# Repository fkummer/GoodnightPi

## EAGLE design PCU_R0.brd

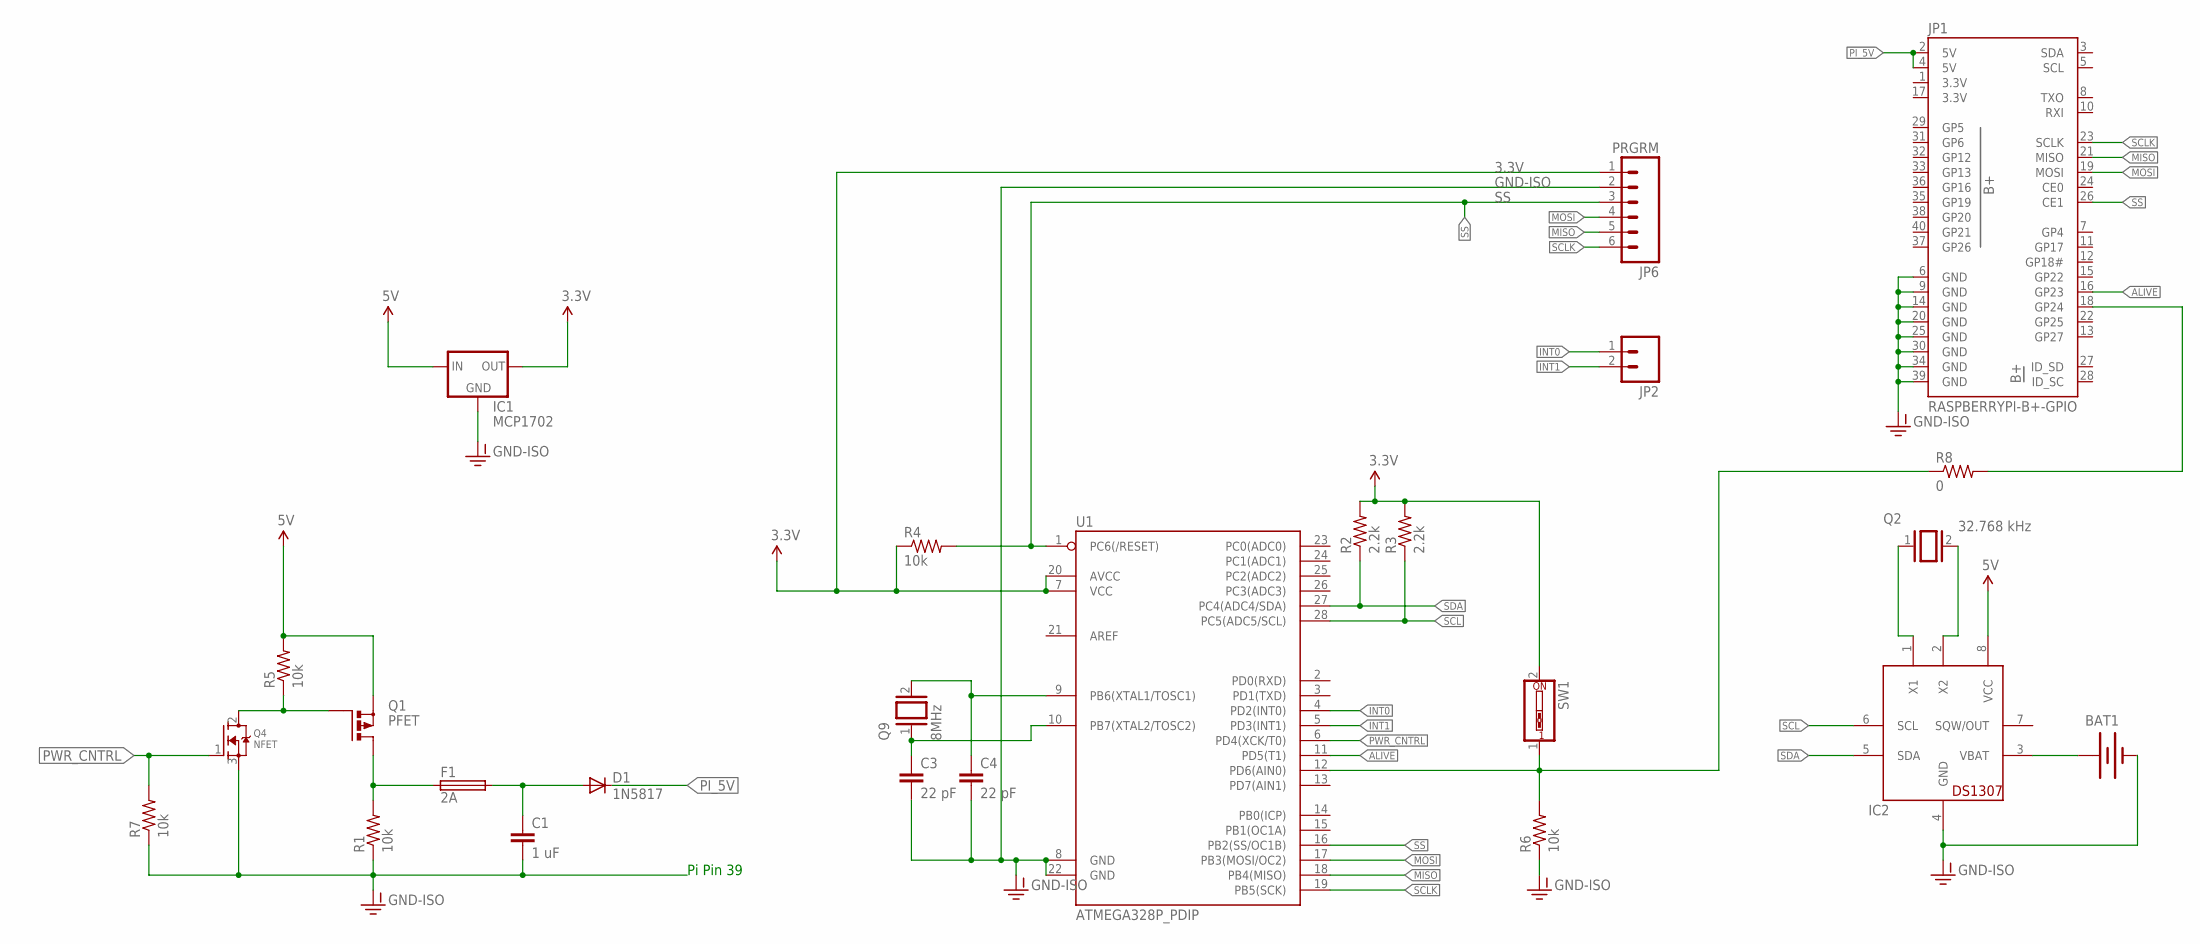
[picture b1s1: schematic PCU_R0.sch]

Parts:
BAT1: BATTERY12MM; BATTCON_12MM
C1: 1 uF; C2.5-3
C3, C4: 22 pF; C2.5-3
D1: 1N5817; DO41-10
F1: 2A; PICOFUSE
IC1: MCP1702; TO92
IC2: DS1307; DIL08
JP1: RASPBERRYPI-B+-GPIO; 2X20-SHROUDED
JP2: M02PTH; 1X02
JP6: PRGRM; 1X06
Q1: PFET; TO220BV
Q2: 32.768 kHz; QS
Q4: NFET; TO220V
Q9: 8MHz; QS
R1, R4, R5, R6, R7: 10k; 1206
R2, R3: 2.2k; 1206
R8: 0; 1206
SW1: SW_DIP-1; EDG-01
U1: ATMEGA328P_PDIP; DIL28-3

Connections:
3.3V: IC1.3 (OUT), JP1.1 (3.3V), JP1.17 (3.3V), JP6.1, R2.2, R3.2, R4.1, SW1.2, U1.7 (VCC), U1.20 (AVCC)
5V: IC1.2 (IN), IC2.8 (VCC), Q1.S, R5.2
ALIVE: JP1.16 (GP23), U1.11 (PD5(T1))
GND-ISO: BAT1.GND (-), C1.2, C3.2, C4.2, IC1.1 (GND), IC2.4 (GND), JP1.6 (GND), JP1.9 (GND), JP1.14 (GND), JP1.20 (GND), JP1.25 (GND), JP1.30 (GND), JP1.34 (GND), JP1.39 (GND), JP6.2, Q4.3 (S), R1.1, R6.1, R7.1, U1.8 (GND), U1.22 (GND)
INT0: JP2.1, U1.4 (PD2(INT0))
INT1: JP2.2, U1.5 (PD3(INT1))
MISO: JP1.21 (MISO), JP6.5, U1.18 (PB4(MISO))
MOSI: JP1.19 (MOSI), JP6.4, U1.17 (PB3(MOSI/OC2))
unnamed: F1.1, Q1.D, R1.2
unnamed: C1.1, D1.A, F1.2
unnamed: IC2.1 (X1), Q2.1
unnamed: IC2.2 (X2), Q2.2
unnamed: BAT1.PWR@1 (+), IC2.3 (VBAT)
unnamed: Q1.G, Q4.2 (D), R5.1
unnamed: JP1.18 (GP24), R8.2
unnamed: R6.2, R8.1, SW1.1, U1.12 (PD6(AIN0))
unnamed: C3.1, Q9.1, U1.10 (PB7(XTAL2/TOSC2))
unnamed: C4.1, Q9.2, U1.9 (PB6(XTAL1/TOSC1))
PI_5V: D1.C, JP1.2 (5V), JP1.4 (5V)
PWR_CNTRL: Q4.1 (G), R7.2, U1.6 (PD4(XCK/T0))
SCL: IC2.6 (SCL), R3.1, U1.28 (PC5(ADC5/SCL))
SCLK: JP1.23 (SCLK), JP6.6, U1.19 (PB5(SCK))
SDA: IC2.5 (SDA), R2.1, U1.27 (PC4(ADC4/SDA))
SS: JP1.26 (CE1), JP6.3, R4.2, U1.1 (PC6(/RESET)), U1.16 (PB2(SS/OC1B))

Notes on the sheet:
Pi Pin 39

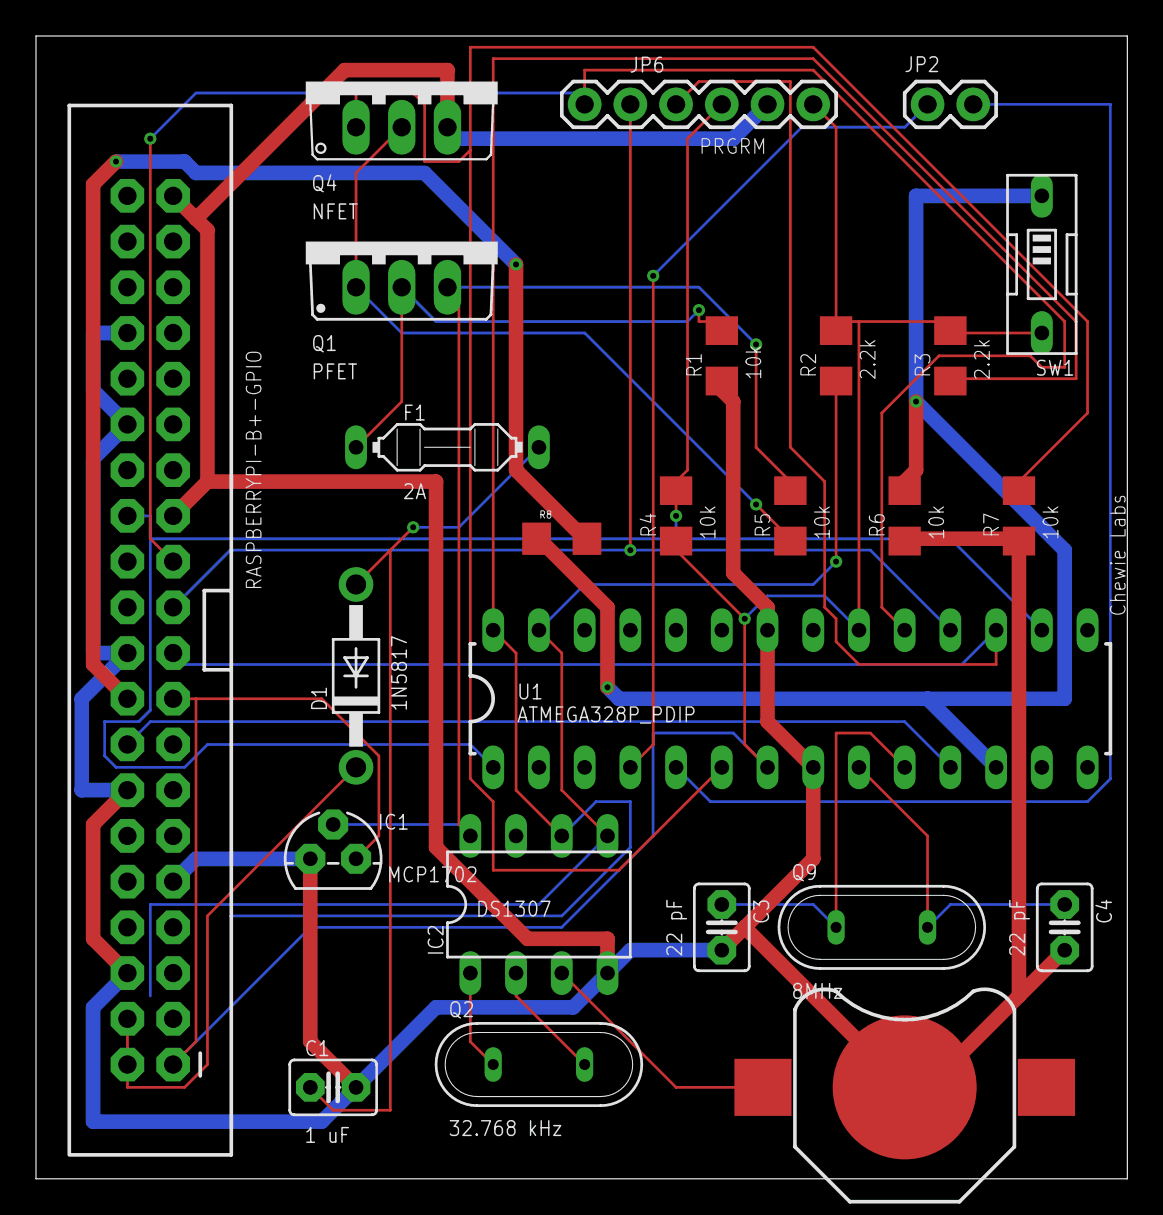
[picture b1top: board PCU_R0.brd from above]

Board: 2 copper layers, 60.6 x 63.5 mm, 25 parts (0 on the bottom side), 24 nets.

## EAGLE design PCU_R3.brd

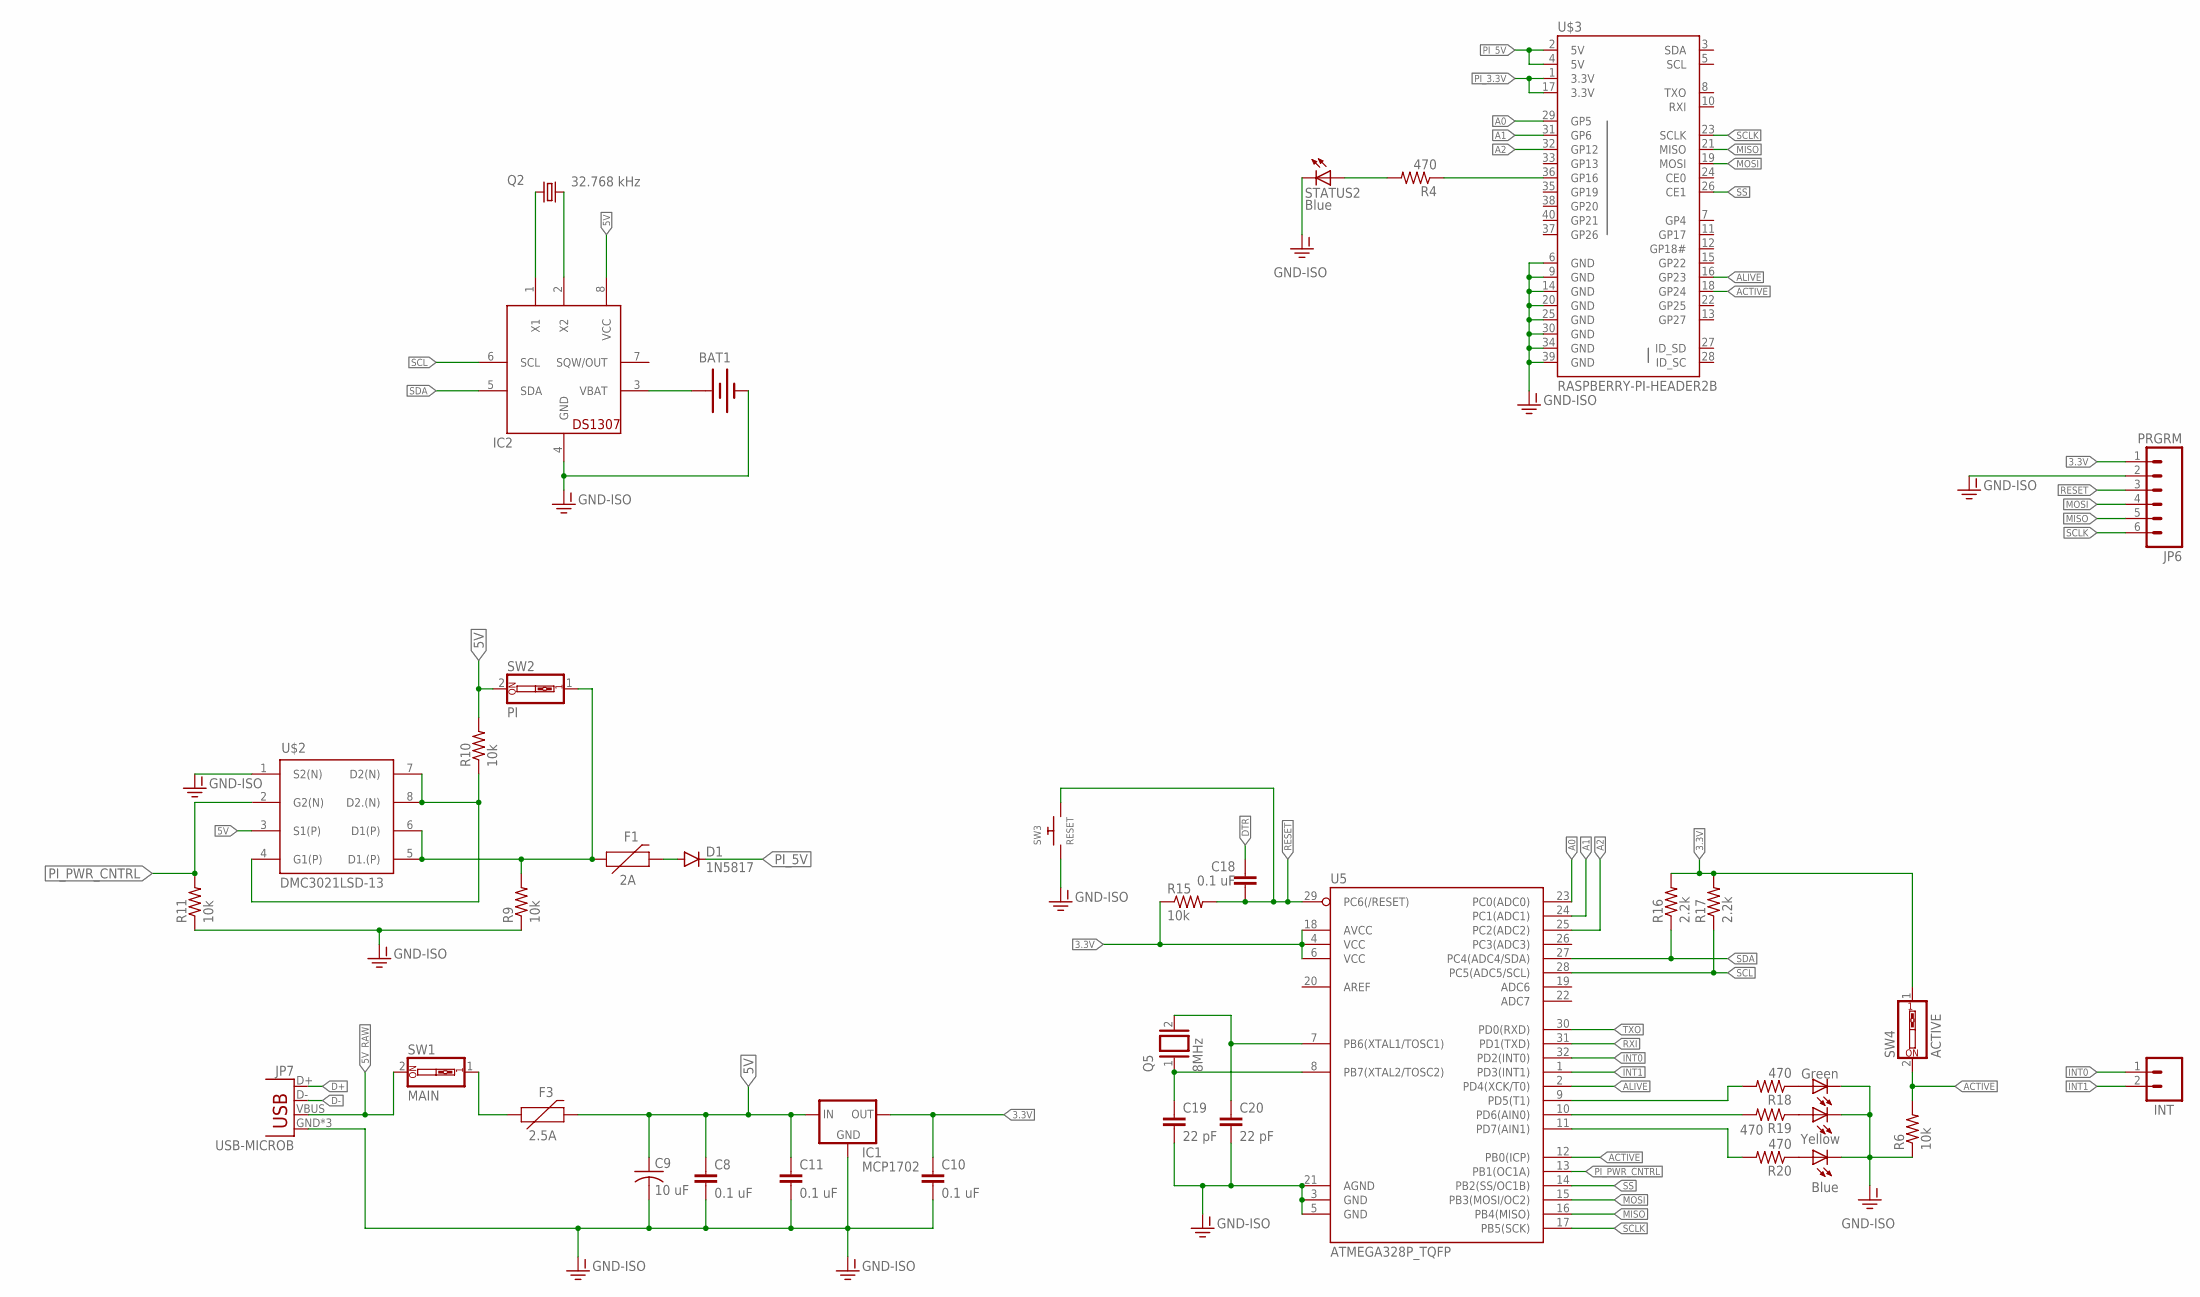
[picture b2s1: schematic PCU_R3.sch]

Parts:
BAT1: BATTERY12MM; BATTCON_12MM
C8, C10, C11, C18: 0.1 uF; 1206
C9: 10 uF; C1206
C19, C20: 22 pF; 1206
D1: 1N5817; DIODE-1N4001
F1: 2A; 1206
F3: 2.5A; 1206
IC1: MCP1702; TO92
IC2: DS1307; DIL08
INT: M02PTH; 1X02
JP6: PRGRM; 1X06
JP7: USB-MICROB
LED6: Green; CHIPLED_1206
LED7: Yellow; CHIPLED_1206
LED8: Blue; CHIPLED_1206
Q2: 32.768 kHz; TC38H
Q5: 8MHz; QS
R4, R18, R19, R20: 470; 1206
R6, R15: 10k; 1206
R9, R10, R11: 10k; R1206
R16, R17: 2.2k; 1206
STATUS2: Blue; CHIPLED_1206
SW1: MAIN; EDG-01
SW2: PI; EDG-01
SW3: RESET; PUSHBUTTON_SMD_SJ
SW4: ACTIVE; EDG-01
U5: ATMEGA328P_TQFP; TQFP32-08
U$2: DMC3021LSD-13; SOIC-8
U$3: RASPBERRY-PI-HEADER2B; 2X20-NOSILK

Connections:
3.3V: C10.1, IC1.3 (OUT), JP6.1, R15.1, R16.2, R17.2, SW4.1, U5.4 (VCC), U5.6 (VCC), U5.18 (AVCC)
5V: C8.1, C9.1, C11.1, F3.2, IC1.2 (IN), IC2.8 (VCC), R10.2, SW2.2, U$2.3 (S1(P))
5V_RAW: JP7.VBUS, SW1.2
5V_SWITCH: F3.1, SW1.1
A0: U5.23 (PC0(ADC0)), U$3.29 (GP5)
A1: U5.24 (PC1(ADC1)), U$3.31 (GP6)
A2: U5.25 (PC2(ADC2)), U$3.32 (GP12)
ACTIVE: R6.2, SW4.2, U5.12 (PB0(ICP)), U$3.18 (GP24)
ALIVE: U5.2 (PD4(XCK/T0)), U$3.16 (GP23)
D+: JP7.D+
D-: JP7.D-
DTR: C18.1
FUSE_DIODE_PI: D1.A, F1.2
GND-ISO: BAT1.GND (-), C8.2, C9.2, C10.2, C11.2, C19.2, C20.2, IC1.1 (GND), IC2.4 (GND), JP6.2, JP7.GND, JP7.MT1 (GND), JP7.MT2 (GND), LED6.C, LED7.C, LED8.C, R6.1, R9.1, R11.1, STATUS2.C, SW3.P$1, U5.3 (GND), U5.5 (GND), U5.21 (AGND), U$2.1 (S2(N)), U$3.6 (GND), U$3.9 (GND), U$3.14 (GND), U$3.20 (GND), U$3.25 (GND), U$3.30 (GND), U$3.34 (GND), U$3.39 (GND)
GP16: R4.1, U$3.36 (GP16)
INT0: INT.1, U5.32 (PD2(INT0))
INT1: INT.2, U5.1 (PD3(INT1))
MISO: JP6.5, U5.16 (PB4(MISO)), U$3.21 (MISO)
MOSI: JP6.4, U5.15 (PB3(MOSI/OC2)), U$3.19 (MOSI)
unnamed: IC2.1 (X1), Q2.1
unnamed: IC2.2 (X2), Q2.2
unnamed: BAT1.PWR@1 (+), IC2.3 (VBAT)
unnamed: R4.2, STATUS2.A
unnamed: LED6.A, R18.1
unnamed: LED7.A, R19.1
unnamed: LED8.A, R20.1
PD5: R18.2, U5.9 (PD5(T1))
PD6: R19.2, U5.10 (PD6(AIN0))
PD7: R20.2, U5.11 (PD7(AIN1))
PI_3.3V: U$3.1 (3.3V), U$3.17 (3.3V)
PI_5V: D1.C, U$3.2 (5V), U$3.4 (5V)
PI_N_DRAIN: R10.1, U$2.4 (G1(P)), U$2.7 (D2(N)), U$2.8 (D2.(N))
PI_PWR_CNTRL: R11.2, U5.13 (PB1(OC1A)), U$2.2 (G2(N))
PI_P_DRAIN: F1.1, R9.2, SW2.1, U$2.5 (D1.(P)), U$2.6 (D1(P))
RESET: C18.2, JP6.3, R15.2, SW3.P$2, U5.29 (PC6(/RESET))
RXI: U5.31 (PD1(TXD))
SCL: IC2.6 (SCL), R17.1, U5.28 (PC5(ADC5/SCL))
SCLK: JP6.6, U5.17 (PB5(SCK)), U$3.23 (SCLK)
SDA: IC2.5 (SDA), R16.1, U5.27 (PC4(ADC4/SDA))
SS: U5.14 (PB2(SS/OC1B)), U$3.26 (CE1)
TXO: U5.30 (PD0(RXD))
XTAL1: C20.1, Q5.2, U5.7 (PB6(XTAL1/TOSC1))
XTAL2: C19.1, Q5.1, U5.8 (PB7(XTAL2/TOSC2))

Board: 2 copper layers, 40 parts (0 on the bottom side), 38 nets, no tracks yet.

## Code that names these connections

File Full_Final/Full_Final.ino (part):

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volatile byte supress_int = 0;

//Is Pi alive
boolean alive = 1;

//Do we want to turn off the power when we get the chance?
boolean gotoSleep = 0;
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long timeInterval = 0;

//Is int0 enabled
byte int0 = 0;

//Is int1 enable
byte int1 = 0;

//timer wants us to get up
byte timer_woke = 0;
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
#define LED   7
#define PACKET_LEN 11
#define ALIVE 4
#define PWR_CNTRL 9
#define INT0 2
#define INT1 3
#define GREEN 6
#define YELLOW 5

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      if(buff[5] == 1){
        Serial.println("\n\ntoggle int0");
        Serial.print("INT0:");
        int0 ^= 1;
        Serial.println(int0);
        Serial.println("\n\n");
        
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      //int1 enable/disable
      if(buff[7] == 1){
        Serial.println("toggle int1");
        int1 ^= 1;
      }
      
      break;
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  pinMode(LED, OUTPUT);
  pinMode(GREEN, OUTPUT);
  pinMode(YELLOW, OUTPUT);
  pinMode(PWR_CNTRL, OUTPUT);
  pinMode(ALIVE, INPUT);
  pinMode(INT0, INPUT);
  pinMode(INT1, INPUT);
  
  

  
  attachInterrupt(digitalPinToInterrupt(INT0), int0_handler, RISING);
  attachInterrupt(digitalPinToInterrupt(INT1), int1_handler, RISING);
 
  digitalWrite(GREEN, LOW);
  digitalWrite(YELLOW, HIGH);
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    if(!alive){
      Serial.println("Beep");
      delay(5000); //Wait to make sure Pi is shutdown
      //attachInterrupt(digitalPinToInterrupt(INT0), int0_handler, RISING);
      //attachInterrupt(digitalPinToInterrupt(INT1), int1_handler, RISING);
      turnOffPower();
      wait_for_wake = 1;
      if(timeInterval != 0){
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     Serial.println("BRING!");
     ledState = ledState ^ 1;
     wait_for_wake = 0;
     //detachInterrupt(digitalPinToInterrupt(INT0));
     //detachInterrupt(digitalPinToInterrupt(INT1));
     digitalWrite(LED,ledState);
     turnOnPower();
  }else{
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
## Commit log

2016-11-15 Init Commit
2016-11-15 Changed startup to right path
2016-11-15 Added Arduino Code
2016-11-16 First SPI tests between Arduinos
2016-11-16 Added SPI with a slave response
2016-11-17 Initial communication between Pi and Arduino using SPI
2016-11-17 rtc blinking led
2016-11-17 Starting to make spi for 11 long packets
2016-11-17 Working on testing pi with longer packets
2016-11-18 Working on two way comms...
2016-11-18 Working on SPI
2016-11-21 spi tested from arduino side, 100ms delay required at Pi side to avoid dropping packets. Adding decision.c which parses the messages received
2016-11-29 Changing protocol
2016-11-29 More SPI
2016-11-30 Slave response working
2016-11-30 Began adding functionality to allow for SPI communication on Pi
2016-11-30 Added functions for sending all messages and receiving all responses on Pi
2016-11-30 Slave response on arduino end working, as well as circular buffer
2016-11-30 Handling setting opcodes and payloads now
2016-11-30 Made a change to help debug on fillEmpty
2016-11-30 Adding wake_check
2016-11-30 Tested wake check going to write call
2016-12-01 Addded scripts for each wakeup type and calls to them
2016-12-01 wake_check v1 complete
2016-12-01 Started integrating RTC and SPI
2016-12-01 More progress on actually configuring it
2016-12-02 More gui
2016-12-04 committing the gui and integrated python and c++
2016-12-04 What have we done
2016-12-04 Updated to actually control power
2016-12-04 config response on gui
2016-12-04 ultrasonic
2016-12-05 ultrasonic wakeup
2016-12-05 final
2016-12-05 more final
2016-12-08 SO IT BEGINS
2016-12-08 Added more web stuff
2016-12-08 Added design overview
2016-12-08 Added ATMEGA
2016-12-08 More website
2016-12-08 more
2016-12-08 Added results
2016-12-08 MORE WEBSIIIITE
2016-12-08 Removed unneeded stuff from github
2016-12-08 Adding gui, rtc and handshake for website
2016-12-08 moved full final
2016-12-08 Moved it back
2016-12-08 adding images
2016-12-08 Ending sections
2016-12-09 added image of gui
2016-12-09 added cycle image
2016-12-09 Added testing sect
2016-12-09 Added parts
2016-12-09 Added division of work
2016-12-09 adding pi cycle
2016-12-09 adding division of work
2016-12-09 some fix
2017-03-20 Pi side fixed to use relative paths
2017-03-31 basically working
2017-03-31 Working with eeprom
2017-05-02 added schem

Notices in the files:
parts and their libraries:
SparkFun-DigitalIC: Licensing: Creative Commons ShareAlike 4.0 International - https://creativecommons.org/licenses/by-sa/4.0
